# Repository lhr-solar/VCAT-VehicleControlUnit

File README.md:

# VehicleControlUnit
Vehicle Control Unit (VCU) for the 2027 Longhorn Racing Solar car

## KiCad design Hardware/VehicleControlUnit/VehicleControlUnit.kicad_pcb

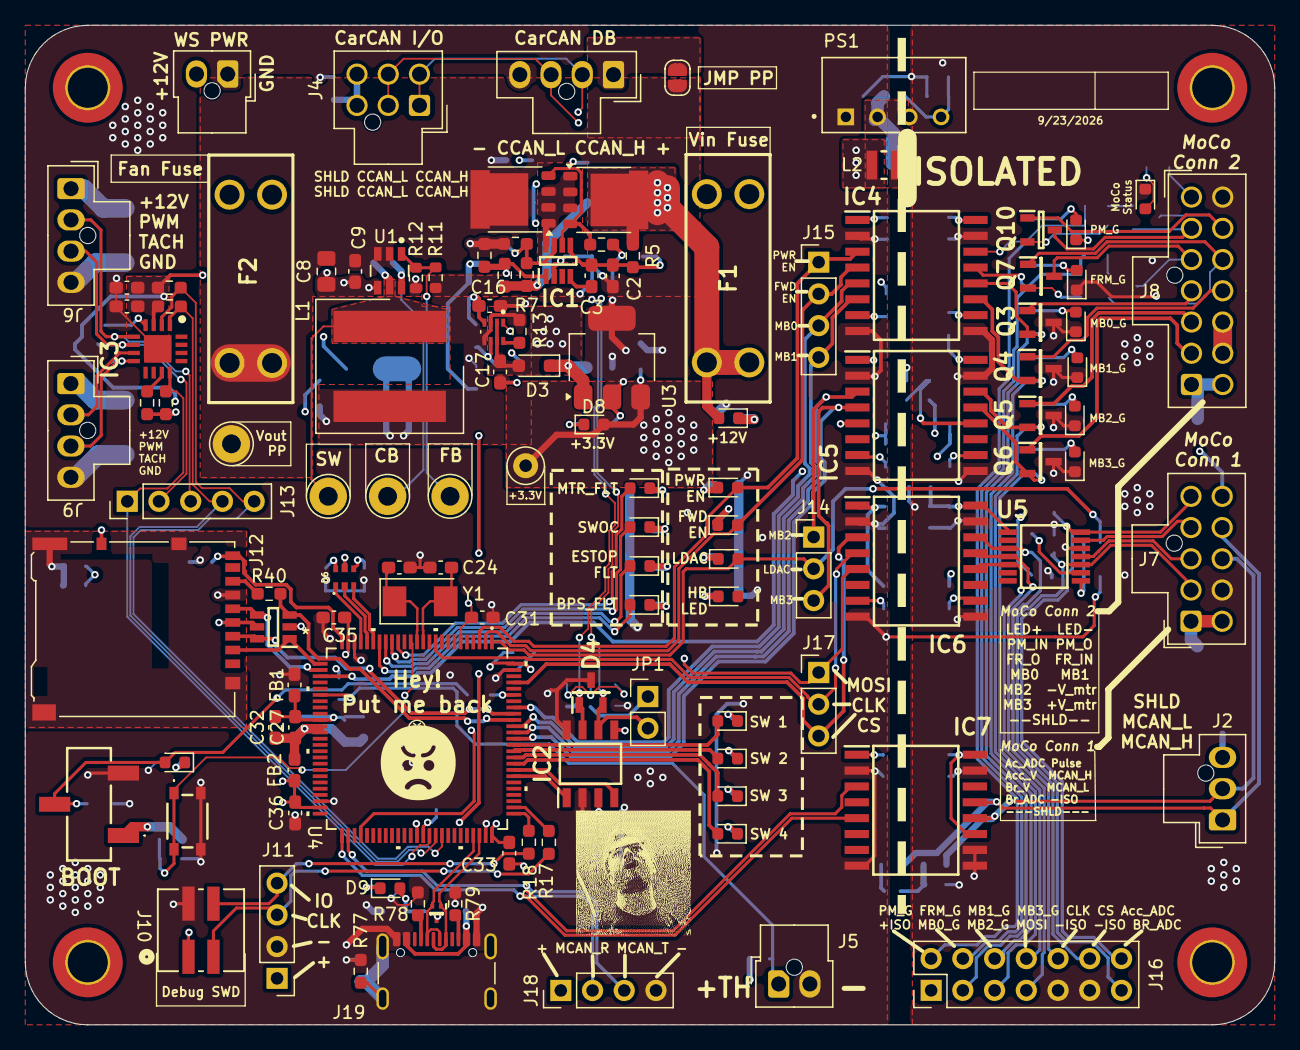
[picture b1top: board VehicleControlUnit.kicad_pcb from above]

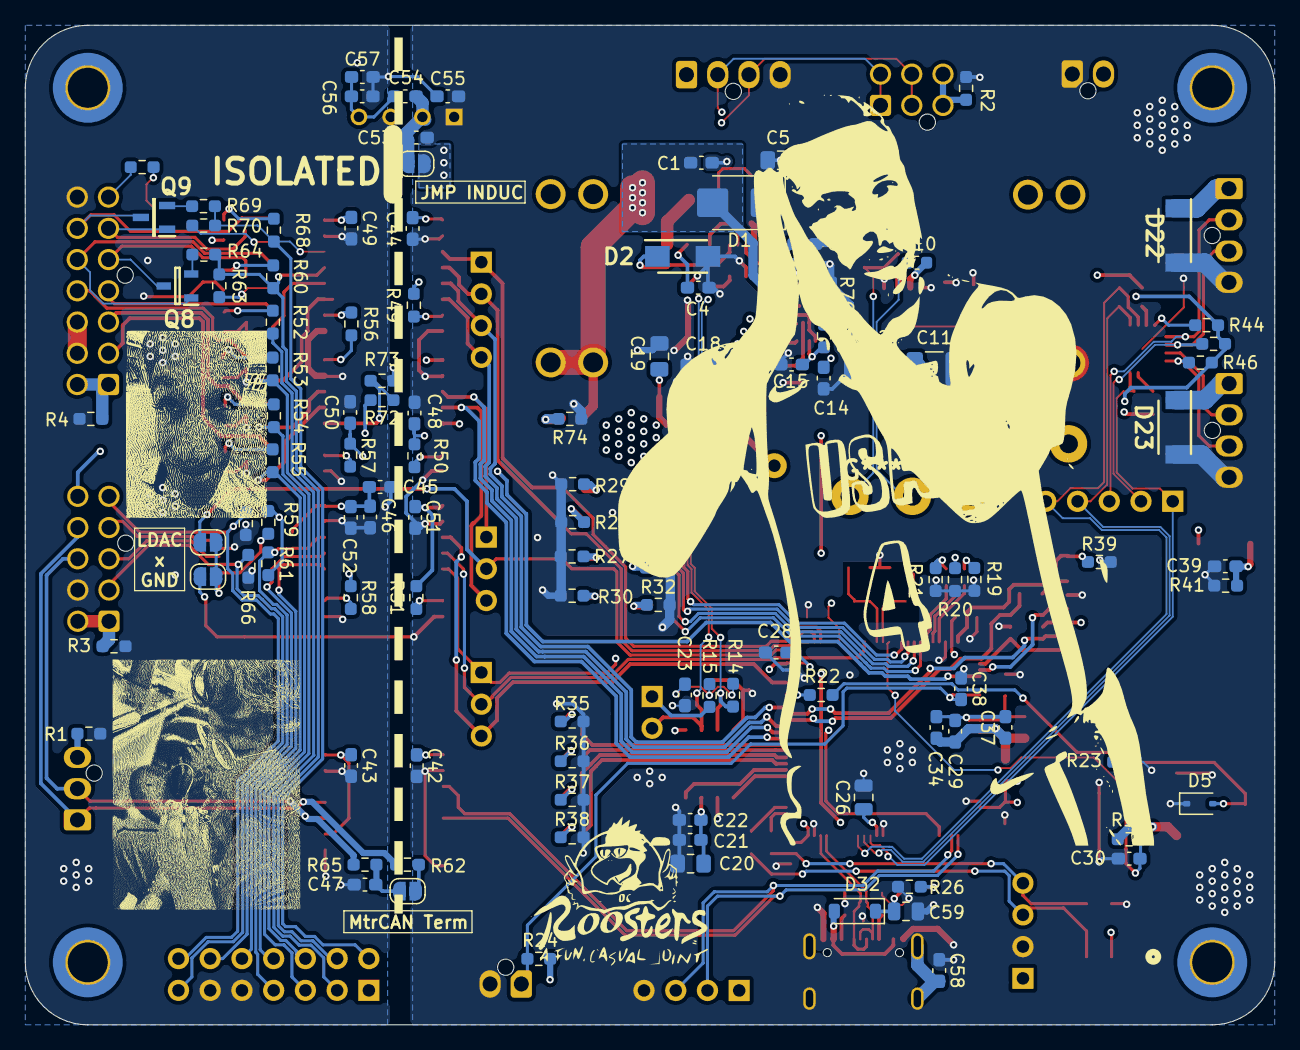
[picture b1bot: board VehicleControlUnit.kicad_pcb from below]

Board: 4 copper layers, 100.0 x 80.0 mm, 238 parts (115 on the bottom side), 160 nets.

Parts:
C1, C6, C7, C21, C22, C23, C27, C28, C29, C30, C31, C33, C35, C36, C37, C42, C43, C44, C47, C48, C49, C50, C51, C52: 0.1u; C_0603_1608Metric_Pad1.08x0.95mm_HandSolder
C2, C32, C34: 1u; C_0603_1608Metric_Pad1.08x0.95mm_HandSolder
C3: 220n; C_0603_1608Metric_Pad1.08x0.95mm_HandSolder
C4: 10n; C_0603_1608Metric_Pad1.08x0.95mm_HandSolder
C5, C18, C19, C20: 10u; C_0805_2012Metric_Pad1.18x1.45mm_HandSolder
C8: 4.7u; C_0805_2012Metric_Pad1.18x1.45mm_HandSolder
C9: 100n; C_0603_1608Metric_Pad1.08x0.95mm_HandSolder
C10: 100n; C_0603_1608Metric
C11, C12: 22u; C_1210_3225Metric_Pad1.33x2.70mm_HandSolder
C13: 3.3u; C_0805_2012Metric_Pad1.18x1.45mm_HandSolder
C14, C15, C16, C17: 0.1uF; C_0603_1608Metric_Pad1.08x0.95mm_HandSolder
C24, C25: 26p; C_0603_1608Metric_Pad1.08x0.95mm_HandSolder
C26: 10u; C_0805_2012Metric
C38, C40, C41: 1uF; C_0603_1608Metric_Pad1.08x0.95mm_HandSolder
C39, C58: 4.7nF; C_0603_1608Metric_Pad1.08x0.95mm_HandSolder
C45: 10u; C_0603_1608Metric_Pad1.08x0.95mm_HandSolder
C46: .1u; C_0603_1608Metric_Pad1.08x0.95mm_HandSolder
C53, C57: 4.7uF; C_0603_1608Metric_Pad1.08x0.95mm_HandSolder
C54, C55: 330pF; C_0603_1608Metric_Pad1.08x0.95mm_HandSolder
C56: 100nF; C_0603_1608Metric_Pad1.08x0.95mm_HandSolder
C59: 10uF; C_0805_2012Metric
CR1: D5V0P4UR6SO-7
D1: SMBJ15CA; D_SMB
D2: SMAF4758A; SODFL5026X125N
D3: SBA130CH-AU_R1_000A1; D_SOD-323_HandSoldering
D4: CDSOT23-T24CAN
D5: TVS; D_SOD-323
D6: RGB_LED
D7, D8, D9, D10, D11, D12, D13, D14, D15, D16, D17, D18, D19, D20, D21, D24, D25, D26, D27, D28, D29, D31: LED; LED_0603_1608Metric
D22, D23: D_Schottky; SODFL5226X100N
D30: LTST-C193KFKT-5A; LED_0603_1608Metric
D32: D_Schottky; D_SOD-123
D33: TPD2EUSB30DRTR
F1, F2: Fuse; Fuse-3557-2
FB1, FB2: FerriteBead; C_0603_1608Metric_Pad1.08x0.95mm_HandSolder
H1, H2, H3, H4: MountingHole; MountingHole_3.2mm_M3_DIN965_Pad_TopBottom
IC1: LM74502DDFR
IC2: TCAN3413DR
IC3: EMC2305-1-AP-TR
IC4, IC5, IC6: ISO7741DWR
IC7: ISO1042QDWRQ1
J1: CAN_DEBUG_NANO_01x04; Molex_Nano-Fit_105309-xx04_1x04_P2.50mm_Vertical
J2: WaveSculptor_CAN; Molex_Nano-Fit_105309-xx03_1x03_P2.50mm_Vertical
J3: WaveSculptor_PWR; Molex_Nano-Fit_105309-xx02_1x02_P2.50mm_Vertical
J4: CAN_NANO_02x03; Molex_Nano-Fit_105310-xx06_2x03_P2.50mm_Vertical
J5: Thermistor; Molex_Nano-Fit_105309-xx02_1x02_P2.50mm_Vertical
J6: Fan_Conn1; Molex_Nano-Fit_105309-xx04_1x04_P2.50mm_Vertical
J7: MotorConn_1; Molex_Nano-Fit_105310-xx10_2x05_P2.50mm_Vertical
J8: Motor_Conn2; custom_2x07_vertical_nanofit
J9: Fan_Conn2; Molex_Nano-Fit_105309-xx04_1x04_P2.50mm_Vertical
J10: SWD_Header; SWD_Conn
J11: SWD; PinHeader_1x04_P2.54mm_Vertical
J12: Micro_SD_Card_Det2; microSD_HC_Hirose_DM3AT-SF-PEJM5
J13: Fan_Debug_Conn; PinHeader_1x05_P2.54mm_Vertical
J14: PH2; PinHeader_1x03_P2.54mm_Vertical
J15: PH1; PinHeader_1x04_P2.54mm_Vertical
J16: Debug_Conn2; PinHeader_2x07_P2.54mm_Vertical
J17: PH3; PinHeader_1x03_P2.54mm_Vertical
J18: PH4; PinHeader_1x04_P2.54mm_Vertical
J19: USB_C_Receptacle_USB2.0_16P; USB_C_Receptacle_GCT_USB4105-xx-A_16P_TopMnt_Horizontal
JP1: TRM; PinHeader_1x02_P2.54mm_Vertical
JP2, JP3, JP4, JP5, JP6: SolderJumper_2_Open; SolderJumper-2_P1.3mm_Open_RoundedPad1.0x1.5mm
L1: 8.2u; 74439369082
L2: 10uH; WE-MAIA_2512
PS1: ROE-3.505S; CONV_ROE-3.305S
Q1, Q2: PSMN012-100YS; LFPAK56
Q3, Q4, Q5, Q6, Q7, Q9: IRLML2030TRPBF
Q8, Q10: DMP3099L-7
R1, R2, R3, R4, R63, R64, R69, R70: 0; R_0603_1608Metric_Pad0.98x0.95mm_HandSolder
R5, R13, R16, R22, R39, R42, R43, R47, R49, R50, R51, R56, R57, R58, R59, R61, R66, R67: 10k; R_0603_1608Metric_Pad0.98x0.95mm_HandSolder
R6: 33; R_0603_1608Metric_Pad0.98x0.95mm_HandSolder
R7, R9, R24: 100k; R_0603_1608Metric_Pad0.98x0.95mm_HandSolder
R8: 7.32k; R_0603_1608Metric_Pad0.98x0.95mm_HandSolder
R10: 15.8k; R_0603_1608Metric_Pad0.98x0.95mm_HandSolder
R11: 100k; R_0603_1608Metric
R12: 19.1k; R_0603_1608Metric
R14, R15, R62, R65: 60; R_0603_1608Metric_Pad0.98x0.95mm_HandSolder
R17, R18: 22; R_0603_1608Metric_Pad0.98x0.95mm_HandSolder
R19, R20, R21, R23, R52, R53, R54, R55, R60, R68: 1k; R_0603_1608Metric_Pad0.98x0.95mm_HandSolder
R25, R27, R28, R29, R30, R31, R32, R33, R34, R35, R36, R37, R38: 250; R_0603_1608Metric_Pad0.98x0.95mm_HandSolder
R26: 2k; R_0603_1608Metric_Pad0.98x0.95mm_HandSolder
R40: 49.9; R_0603_1608Metric_Pad0.98x0.95mm_HandSolder
R41, R77: 1M; R_0603_1608Metric_Pad0.98x0.95mm_HandSolder
R44, R48: 33k; R_0603_1608Metric_Pad0.98x0.95mm_HandSolder
R45, R46, R71, R74: 5k; R_0603_1608Metric_Pad0.98x0.95mm_HandSolder
R72, R78, R79: 5.1k; R_0603_1608Metric_Pad0.98x0.95mm_HandSolder
R73: 9.1k; R_0603_1608Metric_Pad0.98x0.95mm_HandSolder
R75: 16k; R_0603_1608Metric_Pad0.98x0.95mm_HandSolder
R76: 4.7k; R_0603_1608Metric_Pad0.98x0.95mm_HandSolder
Reset1: Reset; TL3365AF180QG
SW1: SW_SPDT; BootSW
TP1: V_in_12V; TestPoint_THTPad_D3.0mm_Drill1.5mm
TP2: CB; TestPoint_THTPad_D3.0mm_Drill1.5mm
TP3: FB; TestPoint_THTPad_D3.0mm_Drill1.5mm
TP4: SW; TestPoint_THTPad_D3.0mm_Drill1.5mm
TP_3.3V1: 3.3V; TestPoint_Loop_D1.80mm_Drill1.0mm_Beaded
U1: LMR51635XDDCR; DDC0006A-MFG
U2: TPS2117DRLR
U3: MCP1826S; SOT-223-3_TabPin2
U4: STM32G473VETx; 100PinMCU
U5: MCP4922T-E/ST; MCP4922T-EST
Y1: Crystal; Crystal_SMD_Abracon_ABM3-2Pin_5.0x3.2mm

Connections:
+3.3V: C19.2, C20.1, C21.1, C22.1, C26.1, C28.1, C31.1, C33.1, C35.1, C36.1, C40.1, C41.1, C42.1, C44.1, C48.1, C51.1, CR1.5, D8.2 (A), FB2.1, IC2.3 (VCC), IC2.5 (SHDNV_IO), IC3.3 (VDD), IC4.1 (VCC1), IC5.1 (VCC1), IC6.1 (VCC1), IC7.1 (VCC1), J10.1, J11.1, J12.4 (VDD), J12.10 (DET_A), J18.1, R16.2, R24.2, R42.1, R43.1, R44.1, R45.2, R46.2, R47.1, R48.1, R49.1, R50.1, R51.1, SW1.1 (A), TP_3.3V1.1 (1_1), U3.3 (VO), U4.6 (VBAT), U4.24 (VDD), U4.49 (VDD), U4.64 (VDD), U4.75 (VDD), U4.100 (VDD)
+5V: C17.1, D3.2 (A), JP5.1 (A), L2.1, U2.2 (VOUT), U2.7 (VOUT__1)
+12V: F1.1, J1.1 (12V), JP6.1 (A)
/+12V_PP: D22.1 (K), D23.1 (K), F2.1, J3.2, J6.1, J9.1
/+TH: C38.2, J5.1, R24.1, U4.31 (PC5)
/Accel_ADC: J7.5, J16.14, R67.2, U5.14 (VA)
/Accel_Vref: J7.4, U5.13 (VrefA)
/BrakeADC: J7.2, J16.13, R66.2, U5.10 (VB)
/Brake_Vref: J7.3, U5.11 (VrefB)
/CarCAN/CAN_RX: IC2.4 (RXD), U4.83 (PD1)
/CarCAN/CAN_TX: IC2.1 (TXD), U4.82 (PD0)
/CarCAN_H: D4.1 (CAN_H), IC2.7 (CANH), J1.2 (CAN_H), J4.1 (CAN_H), J4.6 (CAN_H), R14.1
/CarCAN_L: D4.2 (CAN_L), IC2.6 (CANL), J1.3 (CAN_L), J4.2 (CAN_L), J4.5 (CAN_L), JP1.2 (B)
/FAN1_PWM: IC3.5 (PWM1), J6.2, J13.3
/FAN1_TACH: IC3.6 (TACH1), J6.3, J13.2, R45.1
/FAN2_PWM: IC3.7 (PWM2), J9.2
/FAN2_TACH: IC3.8 (TACH2), J9.3, R46.1
/FR_MODE_IN: J8.5, Q7.3 (S), Q8.3 (S)
/FR_MODE_OUT: J8.10, Q7.1 (D), Q8.1 (D)
/MCU + Peripherals/100PinMCU/BOOT0: R22.1, U4.95 (PB8-BOOT0)
/MCU + Peripherals/100PinMCU/GNDA: C27.2, C29.2, C32.2, C34.2, C37.2, FB1.1, U4.35 (VSSA)
/MCU + Peripherals/100PinMCU/NRST: C30.1, R16.1, Reset1.1, U4.14 (PG10-NRST)
/MCU + Peripherals/100PinMCU/OSC_N: C24.2, U4.12 (PF0-OSC_IN), Y1.2
/MCU + Peripherals/100PinMCU/OSC_P: C25.2, U4.13 (PF1-OSC_OUT), Y1.1
/MCU + Peripherals/100PinMCU/PA0: D6.5, U4.20 (PA0-GPIO_BLUE)
/MCU + Peripherals/100PinMCU/PA1: D6.3, U4.21 (PA1-GPIO_RED)
/MCU + Peripherals/100PinMCU/PA2: D6.1, U4.22 (PA2-GPIO_GREEN)
/MCU + Peripherals/100PinMCU/SWCLK: R17.1, U4.77 (PA14)
/MCU + Peripherals/100PinMCU/SWDIO: R18.1, U4.76 (PA13)
/MCU + Peripherals/100PinMCU/VDDA: C27.1, C29.1, C32.1, C34.1, C37.1, FB2.2, U4.36 (VREF+), U4.37 (VDDA)
/MCU + Peripherals/+5V_USB: C15.1, C59.2, D9.2 (A), D32.1 (K), R75.1, U2.6 (VIN2)
/MCU + Peripherals/ALERT: IC3.12 (ALERT#), J13.1, R47.2, U4.65 (PC6)
/MCU + Peripherals/BPS_Fault: D15.2 (A), U4.19 (PF2)
/MCU + Peripherals/DAC_CLK: IC6.4 (INB), J17.2, U4.10 (PF9)
/MCU + Peripherals/DAC_CS: IC6.3 (INA), J17.3, U4.97 (PE0)
/MCU + Peripherals/DAC_MOSI: IC6.5 (INC), J17.1, U4.54 (PB15)
/MCU + Peripherals/DET: J12.9 (DET_B), R39.1, U4.25 (PA3)
/MCU + Peripherals/ESTOP_Fault: D16.2 (A), U4.18 (PC3)
/MCU + Peripherals/FWD_EN: D11.2 (A), IC4.4 (INB), J15.2, U4.2 (PE3)
/MCU + Peripherals/LDAC: D10.2 (A), J14.2, JP2.1 (A), U4.1 (PE2)
/MCU + Peripherals/MtrCAN_RX: IC7.5 (RXD), J18.2, U4.51 (PB12)
/MCU + Peripherals/MtrCAN_TX: IC7.3 (TXD), J18.3, U4.52 (PB13)
/MCU + Peripherals/Mtr_Fault: D14.2 (A), U4.16 (PC1)
/MCU + Peripherals/PWR_EN: D12.2 (A), IC4.3 (INA), J15.1, U4.3 (PE4)
/MCU + Peripherals/Pulse_ADC4: IC5.5 (INC), U4.28 (PA6)
/MCU + Peripherals/SCL: IC3.2 (SMCLK), J13.5, R43.2, U4.67 (PC8)
/MCU + Peripherals/SDA: IC3.1 (SMDATA), J13.4, R42.2, U4.66 (PC7)
/MCU + Peripherals/SD_CLK: CR1.4, J12.5 (CLK), U4.27 (PA5)
/MCU + Peripherals/SD_CS: CR1.1, J12.2 (DAT3/CD), U4.26 (PA4)
/MCU + Peripherals/SD_MISO: CR1.3, R40.2, U4.91 (PB4)
/MCU + Peripherals/SD_MOSI: CR1.6, J12.3 (CMD), U4.92 (PB5)
/MCU + Peripherals/SWOC: D17.2 (A), U4.17 (PC2)
/MCU + Peripherals/SW_LED1: D18.2 (A), U4.87 (PD5)
/MCU + Peripherals/SW_LED2: D19.2 (A), U4.86 (PD4)
/MCU + Peripherals/SW_LED3: D20.2 (A), U4.85 (PD3)
/MCU + Peripherals/SW_LED4: D21.2 (A), U4.84 (PD2)
/MCU + Peripherals/USB-C Connector/CC1: J19.A5 (CC1), R78.2
/MCU + Peripherals/USB-C Connector/CC2: J19.B5 (CC2), R79.2
/MCU + Peripherals/USB-C Connector/VBUS_IN: D32.2 (A), J19.A4 (VBUS), J19.A9 (VBUS), J19.B4 (VBUS), J19.B9 (VBUS)
/MCU + Peripherals/USB_N: D33.2 (D-), J19.A7 (D-), J19.B7 (D-), U4.72 (PA11)
/MCU + Peripherals/USB_P: D33.1 (D+), J19.A6 (D+), J19.B6 (D+), U4.73 (PA12)
/MTR_CANH: IC7.13 (CANH), J2.1 (CAN_H), J7.7, R62.1
/MTR_CANL: IC7.12 (CANL), J2.2 (CAN_L), J7.8, R65.2
/Moco_LED+: J8.7, R71.1
/Motor Comms/+5V_ISO: C43.1, C45.2, C46.2, C49.1, C50.1, C52.1, C54.1, C56.1, C57.1, IC4.16 (VCC), IC5.16 (VCC), IC6.16 (VCC), IC7.11 (VCC2_1), IC7.16 (VCC2_2), J16.1, PS1.4 (+VOUT), R56.1, R57.1, R58.1, R59.2, R61.2, U5.1 (Vdd)
/Motor Comms/+5V_in: C53.1, C54.2, JP5.2 (B), L2.2, PS1.2 (+VIN)
/Motor Comms/F/R_Mode_Gate: IC4.13 (OUTB), J16.4, R60.2, R63.2, R64.2
/Motor Comms/Map_Bit0_Gate: IC4.12 (OUTC), J16.3, Q3.2 (G), R52.2
/Motor Comms/Map_Bit1_Gate: IC4.11 (IND), J16.6, Q4.2 (G), R53.2
/Motor Comms/Map_Bit2_Gate: IC5.14 (OUTA), J16.5, Q5.2 (G), R54.2
/Motor Comms/Map_Bit3_Gate: IC5.13 (OUTB), J16.8, Q6.2 (G), R55.2
/Motor Comms/Pulse_ADC_DIV: IC5.12 (OUTC), R72.1, R73.1
/Motor Comms/PwrMode_Gate: IC4.14 (OUTA), J16.2, R68.2, R69.1, R70.2
/Motor Comms/SPI_CLK_ISO: IC6.13 (OUTB), J16.10, U5.4 (SCK)
/Motor Comms/SPI_CS_ISO: IC6.14 (OUTA), J16.12, R61.1, U5.3 (~CS)
/Motor Comms/SPI_MOSI_ISO: IC6.12 (OUTC), J16.7, U5.5 (SDI)
/Mtr_Pulse: J7.6, R72.2
/PWR_MODE_IN: J8.6, Q9.1 (D), Q10.3 (S)
/PWR_MODE_OUT: J8.9, Q9.3 (S), Q10.1 (D)
/Power Regulation/5V_Buck: C11.1, C12.1, C13.1, C14.1, L1.2, R11.1, R13.1, U2.3 (VIN1), U2.5 (MODE)
/Power Regulation/12VBuck/CB: C10.1, TP2.1 (1_1), U1.6 (CB)
/Power Regulation/12VBuck/FB: R11.2, R12.1, TP3.1 (1_1), U1.1 (FB)
/Power Regulation/12VBuck/SW: C10.2, L1.1, TP4.1 (1_1), U1.5 (SW)
/Power Regulation/PowerProtection/EN/UVLO: C7.1, IC1.1 (EN/UVLO), R9.2, R10.2
/Power Regulation/PowerProtection/OV: C6.1, IC1.7 (OV), R7.2, R8.1
/Power Regulation/PowerProtection/gate: IC1.6 (GATE), Q1.4, Q2.4, R6.2
/Power Regulation/PowerProtection/source: IC1.8 (SRC), Q1.1, Q1.2, Q1.3, Q2.1, Q2.2, Q2.3
/Power Regulation/Power_Mux/PR1: C16.1, R75.2, R76.1, U2.4 (PR1)
/Power Regulation/Vin_PP: C1.1, D1.2 (A2), D31.2 (A), F1.2, Q1.5, R5.2, R7.1, R9.1
/Power Regulation/Vout_pp: C5.1, C8.1, C9.1, F2.2, JP6.2 (B), Q2.5, TP1.1 (1_1), U1.2 (EN), U1.3 (VIN)
/map_bit0: IC4.5 (INC), J15.3, U4.93 (PB6)
/map_bit0_sig: J8.4, Q3.1 (D)
/map_bit1: IC4.6 (OUTD), J15.4, U4.90 (PB3)
/map_bit1_sig: J8.11, Q4.1 (D)
/map_bit2: IC5.3 (INA), J14.1, U4.89 (PD7)
/map_bit2_sig: J8.3, Q5.1 (D)
/map_bit3: IC5.4 (INB), J14.3, U4.88 (PD6)
/map_bit3_sig: J8.2, Q6.1 (D)
GND: C1.2, C2.1, C4.2, C5.2, C6.2, C7.2, C8.2, C9.2, C11.2, C12.2, C13.2, C14.2, C15.2, C16.2, C17.2, C18.1, C19.1, C20.2, C21.2, C22.2, C23.1, C24.1, C25.1, C26.2, C28.2, C30.2, C31.2, C33.2, C35.2, C36.2, C38.1, C39.1, C40.2, C41.2, C42.2, C44.2, C48.2, C51.2, C53.2, C55.2, C58.1, C59.1, CR1.2, D1.1 (A1), D2.2 (A), D4.3 (GND), D5.1 (A1), D22.2 (A), D23.2 (A), D33.3 (GND), FB1.2, IC1.2 (GND), IC2.2 (GND), IC2.8 (STB), IC3.17 (EP), IC4.2 (GND1_1), IC4.8 (GND1_2), IC5.2 (GND1_1), IC5.8 (GND1_2), IC6.2 (GND1_1), IC6.8 (GND1_2), IC7.2 (GND1_1), IC7.8 (GND1_2), J1.4 (GND), J3.1, J5.2, J6.4, J9.4, J10.2, J11.2, J12.6 (VSS), J18.4, J19.A1 (GND), J19.A12 (GND), J19.B1 (GND), J19.B12 (GND), JP3.1 (A), PS1.1 (-VIN), R2.2, R8.2, R10.1, R12.2, R19.2, R20.2, R21.2, R23.2, R25.2, R26.2, R27.2, R28.2, R29.2, R30.2, R31.2, R32.2, R33.2, R34.2, R35.2, R36.2, R37.2, R38.2, R39.2, R41.1, R74.2, R76.2, R77.1, R78.1, R79.1, Reset1.2, SW1.3 (C), U1.4 (GND), U2.1 (GND), U3.2 (GND), U4.23 (VSS), U4.48 (VSS), U4.63 (VSS), U4.74 (VSS), U4.99 (VSS)
GND_ISO: C43.2, C45.1, C46.1, C47.2, C49.2, C50.2, C52.2, C55.1, C56.2, C57.2, D24.1 (K), D25.1 (K), D26.1 (K), D27.1 (K), D28.1 (K), D29.1 (K), D30.1 (K), IC4.9 (GND2_1), IC4.15 (GND2_2), IC5.9 (GND2_1), IC5.15 (GND2_2), IC6.9 (GND2_1), IC6.15 (GND2_2), IC7.9 (GND2_1), IC7.10 (GND2_2), IC7.15 (GND2_3), J7.9, J8.8, J16.9, J16.11, PS1.3 (-VOUT), Q3.3 (S), Q4.3 (S), Q5.3 (S), Q6.3 (S), R1.1, R3.2, R4.2, R66.1, R67.1, R73.2, U5.12 (Vss)
unnamed: C4.1, R6.1
unnamed: C23.2, R14.2, R15.1
unnamed: C2.2, C3.1, D2.1 (K), IC1.5 (VS), R5.1
unnamed: C18.2, D3.1 (K), U3.1 (VI)
unnamed: D5.2 (A2), D7.2 (A), R22.2, SW1.2 (B)
unnamed: D6.2, R19.1
unnamed: D6.4, R20.1
unnamed: D6.6, R21.1
unnamed: D7.1 (K), R23.1
unnamed: D8.1 (K), R25.1
unnamed: D9.1 (K), R26.1
unnamed: D10.1 (K), R27.1
unnamed: D11.1 (K), R28.1
unnamed: D12.1 (K), R29.1
unnamed: D13.1 (K), R30.1
unnamed: D14.1 (K), R31.1
unnamed: D15.1 (K), R32.1
unnamed: D16.1 (K), R33.1
unnamed: D17.1 (K), R34.1
unnamed: D18.1 (K), R35.1
unnamed: D19.1 (K), R36.1
unnamed: D20.1 (K), R37.1
unnamed: D21.1 (K), R38.1
unnamed: D24.2 (A), R52.1
unnamed: D25.2 (A), R53.1
unnamed: D26.2 (A), R54.1
unnamed: D27.2 (A), R55.1
unnamed: D28.2 (A), R60.1
unnamed: D29.2 (A), R68.1
unnamed: D30.2 (A), R71.2
unnamed: D31.1 (K), R74.1
unnamed: C3.2, IC1.4 (VCAP)
unnamed: IC3.4 (ADDR_SEL), R44.2
unnamed: IC3.11 (CLK), R48.2
unnamed: IC4.7 (EN1), R49.2
unnamed: IC4.10 (EN2), R56.2
unnamed: IC5.7 (EN1), R50.2
unnamed: IC5.10 (EN2), R57.2
unnamed: IC6.7 (EN1), R51.2
unnamed: IC6.10 (EN2), R58.2
unnamed: J2.3 (SHIELD), R1.2
unnamed: J4.3 (SHIELD), J4.4 (SHIELD), R2.1
unnamed: J7.1, J7.10, R3.1
unnamed: J8.1, J8.14, R4.1
unnamed: J8.12, J8.13
unnamed: J10.3, J11.3, R17.2
unnamed: J10.4, J11.4, R18.2
unnamed: J12.7 (DAT0), R40.1
unnamed: C39.2, J12.SH (SHIELD), R41.2
unnamed: C58.2, J19.S1 (SHIELD), J19.S2 (Shield), J19.S3 (Shield), J19.S4 (Shield), R77.2
unnamed: JP1.1 (A), R15.2
unnamed: JP2.2 (B), JP3.2 (B), U5.8 (~LDAC)
unnamed: JP4.1 (A), R62.2
unnamed: C47.1, JP4.2 (B), R65.1
unnamed: Q7.2 (G), R63.1
unnamed: Q8.2 (G), R64.1
unnamed: Q9.2 (G), R69.2
unnamed: Q10.2 (G), R70.1
unnamed: R13.2, U2.8 (ST)
unnamed: R59.1, U5.9 (~SHDN)

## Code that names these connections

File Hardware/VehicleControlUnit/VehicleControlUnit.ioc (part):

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Mcu.Name=STM32G473V(B-C-E)Tx
Mcu.Package=LQFP100
Mcu.UserName=STM32G473VETx
PA0.Signal=GPIO_Output
PA1.Signal=GPIO_Output
PA11.Mode=Device
PA11.Signal=USB_DM
PA12.Mode=Device
PA12.Signal=USB_DP
PA2.Signal=GPIO_Output
PA4.Signal=GPIO_Output
PA5.Mode=Full_Duplex_Master
PA5.Signal=SPI1_SCK
PA6.Mode=IN3-Single-Ended
PA6.Signal=ADC2_IN3
PB12.Mode=FDCAN_Activate
PB12.Signal=FDCAN2_RX
PB13.Mode=FDCAN_Activate
PB13.Signal=FDCAN2_TX
PB14.Mode=Full_Duplex_Master
PB14.Signal=SPI2_MISO
PB15.Mode=Full_Duplex_Master
PB15.Signal=SPI2_MOSI
PB3.Signal=GPIO_Input
PB4.Mode=Full_Duplex_Master
PB4.Signal=SPI1_MISO
PB5.Mode=Full_Duplex_Master
PB5.Signal=SPI1_MOSI
PC0.Mode=IN6-Single-Ended
PC0.Signal=ADC2_IN6
PC10.Mode=Full_Duplex_Master
PC10.Signal=SPI3_SCK
PC11.Mode=Full_Duplex_Master
PC11.Signal=SPI3_MISO
PC12.Mode=Full_Duplex_Master
PC12.Signal=SPI3_MOSI
PC13.Signal=GPIO_Output
PC14-OSC32_IN.Signal=GPIO_Output
PC15-OSC32_OUT.Signal=GPIO_Output
PC5.Mode=IN11-Single-Ended
PC5.Signal=ADC2_IN11
PC6.Mode=I2C
PC6.Signal=I2C4_SCL
PC7.Mode=I2C
PC7.Signal=I2C4_SDA
PC8.Signal=GPIO_Input
PC9.Signal=GPIO_Output
PD0.Mode=FDCAN_Activate
PD0.Signal=FDCAN1_RX
PD1.Mode=FDCAN_Activate
PD1.Signal=FDCAN1_TX
PD2.Signal=GPIO_Output
PD3.Signal=GPIO_Output
PD4.Signal=GPIO_Output
PD5.Signal=GPIO_Output
PE0.Signal=GPIO_Output
PE2.Signal=GPIO_Output
PE3.Signal=GPIO_Output
PE4.Signal=GPIO_Output
PF0-OSC_IN.Mode=HSE-External-Oscillator
PF0-OSC_IN.Signal=RCC_OSC_IN
PF1-OSC_OUT.Mode=HSE-External-Oscillator
PF1-OSC_OUT.Signal=RCC_OSC_OUT
PF9.Mode=Full_Duplex_Master
PF9.Signal=SPI2_SCK
RCC.HSE_VALUE=8000000
RCC.SYSCLKFreq_VALUE=16000000
board=custom
